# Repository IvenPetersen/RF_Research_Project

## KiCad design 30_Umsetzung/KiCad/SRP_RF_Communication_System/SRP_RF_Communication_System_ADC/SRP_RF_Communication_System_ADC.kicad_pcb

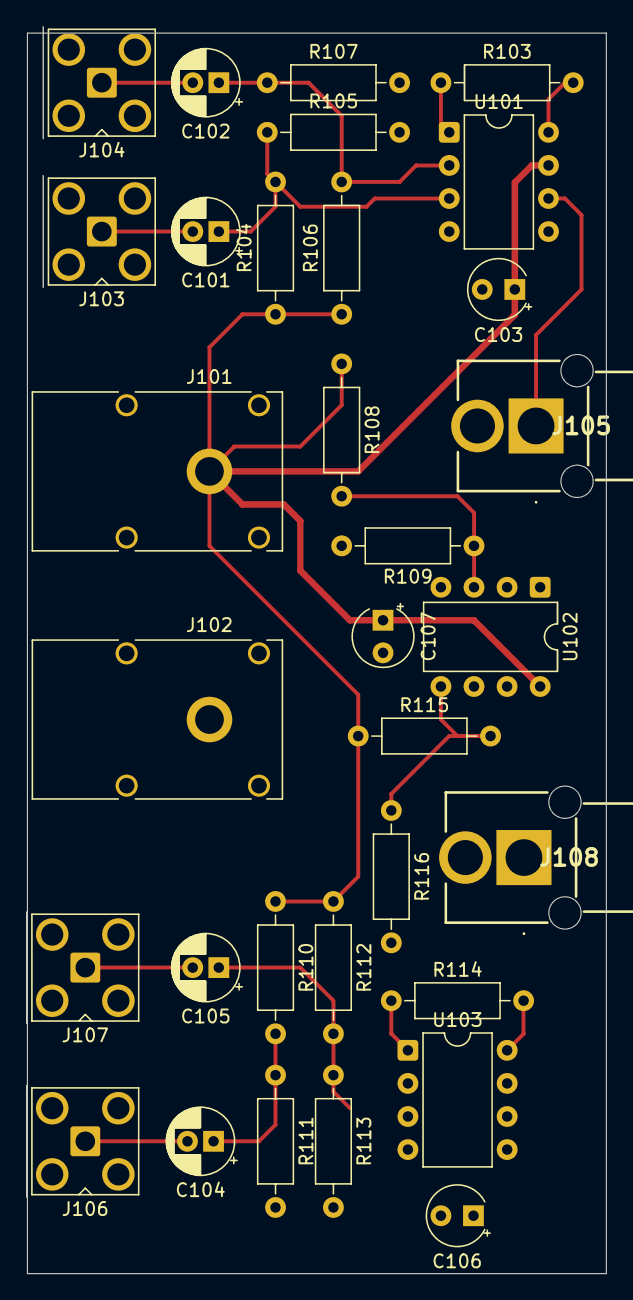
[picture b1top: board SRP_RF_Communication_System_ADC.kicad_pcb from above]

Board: 2 copper layers, 44.5 x 95.7 mm, 32 parts (0 on the bottom side), 20 nets.

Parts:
C101, C102, C104, C105: C_Polarized; CP_Radial_D5.0mm_P2.00mm
C103, C106, C107: 100n; CP_Radial_Tantal_D4.5mm_P2.50mm
J101: banana_conn_red; Banana_Cliff_FCR7350R_S16N-PC_Horizontal
J102: banana_conn_black; Banana_Cliff_FCR7350B_S16N-PC_Horizontal
J103, J106: sma_conn_I+; SMA_Amphenol_901-143_Horizontal
J104, J107: sma_conn_I-; SMA_Amphenol_901-143_Horizontal
J105, J108: chinch_conn_I; RCJ047
R103, R114: 50k; R_Axial_DIN0207_L6.3mm_D2.5mm_P10.16mm_Horizontal
R104, R106, R108, R110, R112, R115: 3k; R_Axial_DIN0207_L6.3mm_D2.5mm_P10.16mm_Horizontal
R105, R107, R109, R111, R113, R116: 1.5k; R_Axial_DIN0207_L6.3mm_D2.5mm_P10.16mm_Horizontal
U101, U103: INA128; DIP-8_W7.62mm
U102: TS922IN; DIP-8_W7.62mm

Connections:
+5V: C103.1, C106.1, C107.1, J101.1, R104.1, R106.1, R108.1, R110.1, R112.1, R115.1, U101.7 (V+), U102.8 (V+), U103.7 (V+)
GND: C103.2, C106.2, C107.2, J102.1, J103.2 (Ext), J104.2 (Ext), J105.2 (Ext), J106.2 (Ext), J107.2 (Ext), J108.2 (Ext), R105.2, R107.2, R109.2, R111.2, R113.2, R116.2, U101.4 (V-), U102.4 (V-), U103.4 (V-)
unnamed: C101.2, J103.1 (In)
unnamed: C102.2, J104.1 (In)
unnamed: J105.1 (In), U101.6
unnamed: C104.2, J106.1 (In)
unnamed: C105.2, J107.1 (In)
unnamed: J108.1 (In), U103.6
unnamed: R103.1, U101.1 (Rg)
unnamed: R103.2, U101.8 (Rg)
unnamed: R114.1, U103.1 (Rg)
unnamed: R114.2, U103.8 (Rg)
unnamed: C101.1, R104.2, R105.1, U101.3 (+)
unnamed: C102.1, R106.2, R107.1, U101.2 (-)
unnamed: U101.5 (Ref), U102.1, U102.2 (-)
unnamed: R108.2, R109.1, U102.3 (+)
unnamed: R115.2, R116.1, U102.5 (+)
unnamed: U102.6 (-), U102.7, U103.5 (Ref)
unnamed: C104.1, R110.2, R111.1, U103.3 (+)
unnamed: C105.1, R112.2, R113.1, U103.2 (-)

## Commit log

2025-10-21 Neue Ordner und Namen
2025-10-21 Test
2025-10-21 Test Done
2025-10-21 neue Dateien
2025-10-21 Project plan update
2025-10-30 30.10.25
2025-10-30 Create Mikrofonaufnahme_Echtzeit_USB.m
    Matlab-Code für Aufnahme in Echtzeit des Mikrofonsignals
2025-11-01 Update arduino_ppl_code.ino
    PLL ist Fertig
2025-11-01 renamed files
    ppl sollte pll heißen
2025-11-01 Create serial_arduino_test.m
    done
2025-11-02 Kleine Änderungen
2025-11-02 Erster Matlab-Code zum Empfänger mit Plot Zeitsignal und FFT
2025-11-02 Weitere potenzielle Änderungen
2025-11-04 test1 added
2025-11-04 added timer
2025-11-04 dac/code.ino added
2025-11-04 Erstes gemessenes Spektrum eines Sinus-Signals unterschiedlicher Frequenz
2025-11-04 Unnötiger Ordner gelöscht
2025-11-04 04.11.25
2025-11-04 Konstanter Signalton
2025-11-04 Durchgängiger Signalton
2025-11-04 new code for signalgenarator added
2025-11-06 Verhindern der Harmonischen durch bessere Abtastung
2025-11-10 Konstante Ausgabe bei 100 kHz
2025-11-10 Add Arduino class-based PLL and Modulator
    New functions:
    F= [You'reFrequencyInMHz] now also changes the MODULATOR registers.
    MOD_NegativGain control via serial: MOD_NegativGain= [You'reNegativGainIn_dB]
    MOD_QDISABLE control via serial: MOD_QDISABLE= [1 or 0]
2025-11-11 Zero Padding und korrekte Amplitude
2025-11-11 moved old files in archiv folder
2025-11-11 new files added: Dual SG's up to 25kHz
2025-11-12 work from 11.11.25
2025-11-18 ADC ein Kanal korrekte Plots
2025-11-22 Besserer Plot. Weiterhin Buffer Probleme
2025-11-23 Korrekte Ausgabe tiefer Signaltöne
2025-11-23 Synchronisation Plot und Audioausgabe
2025-11-24 Ein Kanal 80 kHz funktionstüchtig
2025-11-24 Refactor SPI register writes and update command interface
    Refactored SPI register write functions to ensure proper transaction handling and improved debug output. Updated serial command interface for modulator settings to use shorter command names (MOD_NG a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
2025-11-25 Zwei Kanäle Sicherheitskopie
2025-11-25 Zwei Kanäle funktionstüchtig
2025-11-26 Add LTC5594 demodulator support and update modulator logic
    Introduced LTC5594 demodulator class and integration in the Arduino test project, including new commands for demodulator control. Updated modulator QDISABLE logic to use uint8_t instead of bool and f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
2025-11-28 Offset korrigiert
2025-11-30 Update data
2025-12-09 New LTspice
2025-12-11 Leistungsunabhängigeres Programm in Empfaener
2025-12-12 Gesteigerte Effizienz
2025-12-13 Vereinfachung effizienter Code
2025-12-16 Schaltung überarbeitet
2026-01-18 draw.io's erstellt
2026-01-18 Update and add new version of Plakat diagram
    Modified the Plakat.drawio diagram with layout and content changes, and added a new exported image version as Plakat_V2_drawio.png.
